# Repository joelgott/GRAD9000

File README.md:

# Description

This project is strongly inspired by the HAL9000 robot from Stanley Kubrick's 2001 Space Odyssey. I used an ESP32 based board for the main logic and an audio module so that it looks like it's talking. Most of the mechanical parts are recicled or 3D printed.
This repository contains all the contents for making and programming the robot.

## Hardware

This robot uses a [seed studio XIAO ESP32-c3 development board](https://wiki.seeedstudio.com/XIAO_ESP32C3_Getting_Started/) with a [DFPlayer audio module](https://www.dfrobot.com/product-1121.html). 
In the PCB folder there is a custom designed PCB that contains both boards, recieves a 5V input and has, a servo controller connector, an i2c bus output, a rgb led pinout and a speaker output. There is also a socket for an adxl345 accelerometer and other audio output that can go to an amplifier.

## Software

In the Circuitpython folder there is the code that runs on the robot. There are two files, the one called eyetest lets me play with the rgb led to try animations and such. The other one called grad9000 contains the logic for controlling the audio module, reading the json file and switching the green led while maintaining the red one permanently on so that it looks like it's talking. 

## Extras

I also made a python script that lets you generate a json file that contains the information of the audio files. This json file can then be uploaded to the robot so it knows the duration of each audio file and how many are in each folder.

## Contributing

Pull requests are welcome. For major changes, please open an issue first
to discuss what you would like to change.

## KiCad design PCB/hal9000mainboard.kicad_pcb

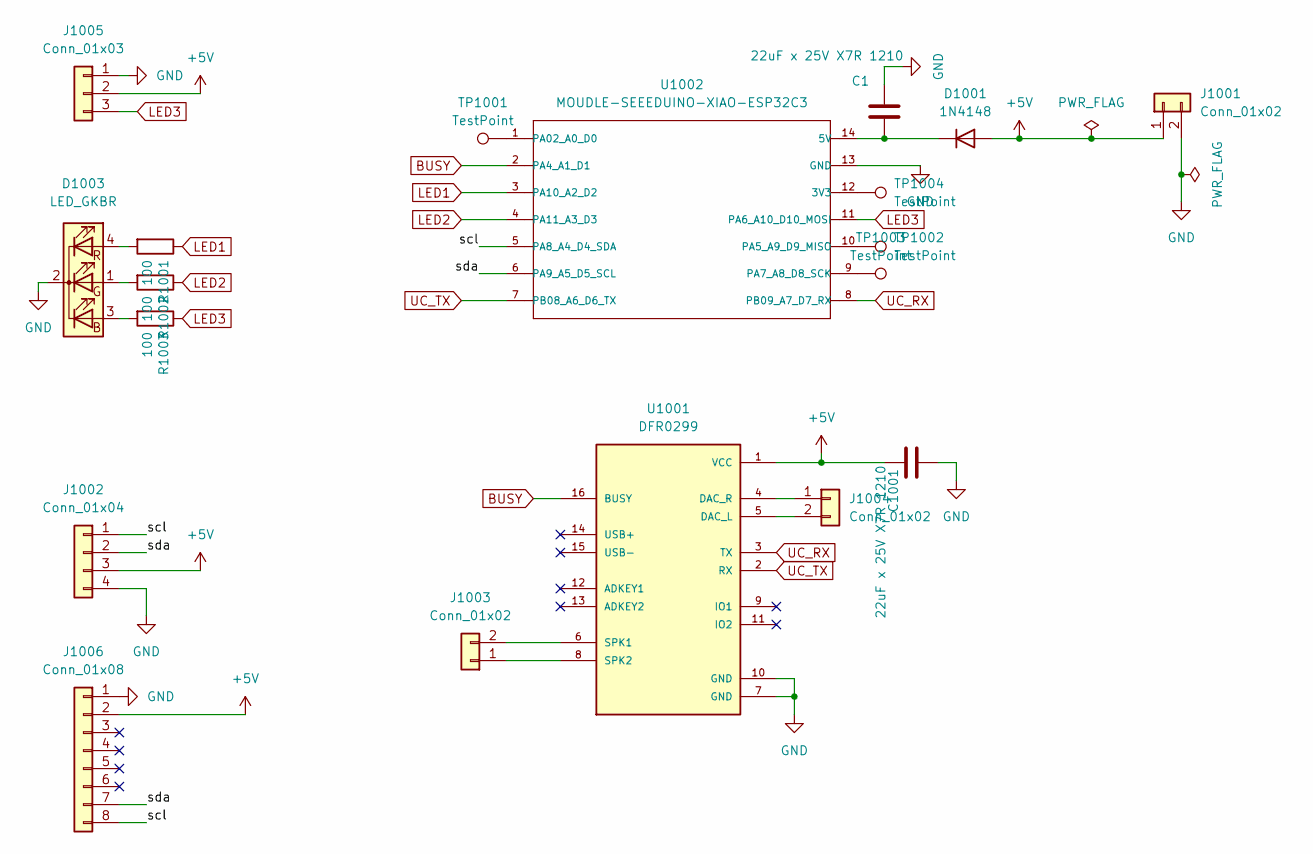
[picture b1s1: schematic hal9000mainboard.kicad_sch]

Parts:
C1, C1001: 22uF x 25V X7R 1210; C_Rect_L4.0mm_W2.5mm_P2.50mm; Digikey Code 1276-3392-1-ND
D1001: 1N4148; D_DO-35_SOD27_P7.62mm_Horizontal
D1003: LED_GKBR; LED_D5.0mm-4_RGB_Wide_Pins
J1001: Conn_01x02; PhoenixContact_MCV_1,5_2-G-3.81_1x02_P3.81mm_Vertical
J1002: Conn_01x04; PinHeader_1x04_P2.54mm_Vertical
J1003, J1004: Conn_01x02; TerminalBlock_bornier-2_P5.08mm
J1005: Conn_01x03; PinHeader_1x03_P2.54mm_Vertical
J1006: Conn_01x08; PinHeader_1x08_P2.54mm_Vertical
R1001, R1002, R1003: 100; R_0603_1608Metric; Digikey Code 2019-RK73H1JRTTD2200FCT-ND
TP1001, TP1002, TP1003, TP1004: TestPoint; TestPoint_Pad_3.0x3.0mm
U1001: DFR0299; MODULE_DFR0299
U1002: MOUDLE-SEEEDUINO-XIAO-ESP32C3; XIAO-Generic-Hybrid-14P-2.54-21X17.8MM

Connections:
+5V: C1001.1, D1001.2 (A), J1001.1, J1002.3, J1005.2, J1006.2, U1001.1 (VCC)
/scl: J1002.1, J1006.8, U1002.5 (PA8_A4_D4_SDA)
/sda: J1002.2, J1006.7, U1002.6 (PA9_A5_D5_SCL)
BUSY: U1001.16 (BUSY), U1002.2 (PA4_A1_D1)
GND: C1.2, C1001.2, D1003.2 (K), J1001.2, J1002.4, J1005.1, J1006.1, U1001.7 (GND), U1001.10 (GND), U1002.13 (GND)
LED1: R1001.1, U1002.3 (PA10_A2_D2)
LED2: R1002.1, U1002.4 (PA11_A3_D3)
LED3: J1005.3, R1003.1, U1002.11 (PA6_A10_D10_MOSI)
unnamed: C1.1, D1001.1 (K), U1002.14 (5V)
unnamed: D1003.3 (BA), R1003.2
unnamed: D1003.1 (GA), R1002.2
unnamed: D1003.4 (RA), R1001.2
unnamed: J1003.1, U1001.8 (SPK2)
unnamed: J1003.2, U1001.6 (SPK1)
unnamed: J1004.1, U1001.4 (DAC_R)
unnamed: J1004.2, U1001.5 (DAC_L)
unnamed: TP1004.1, U1002.12 (3V3)
unnamed: TP1001.1, U1002.1 (PA02_A0_D0)
unnamed: TP1002.1, U1002.10 (PA5_A9_D9_MISO)
unnamed: TP1003.1, U1002.9 (PA7_A8_D8_SCK)
UC_RX: U1001.3 (TX), U1002.8 (PB09_A7_D7_RX)
UC_TX: U1001.2 (RX), U1002.7 (PB08_A6_D6_TX)

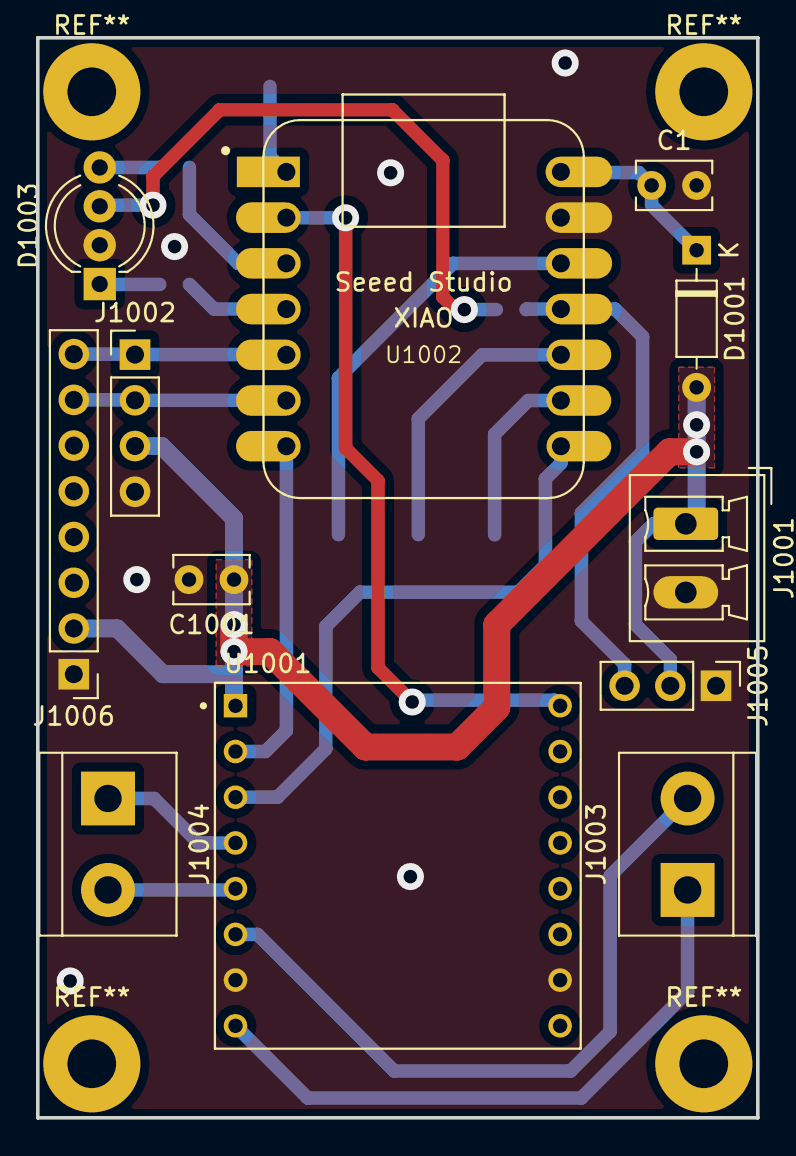
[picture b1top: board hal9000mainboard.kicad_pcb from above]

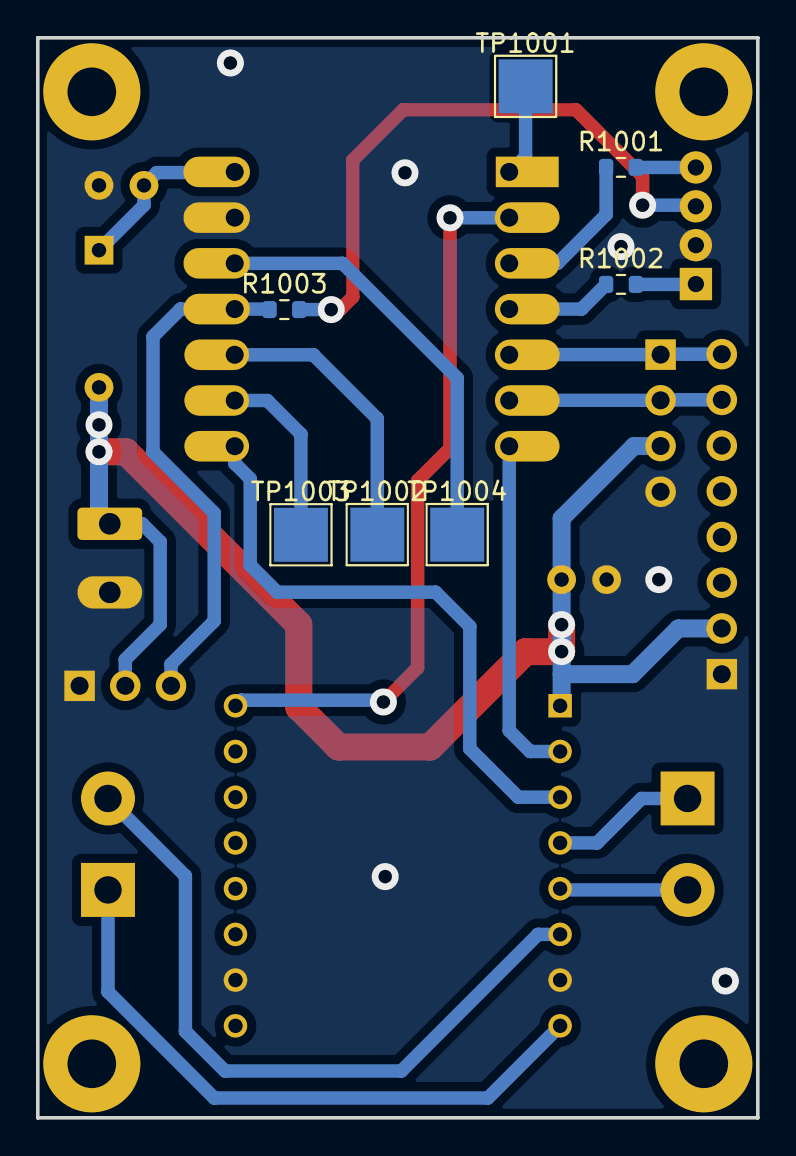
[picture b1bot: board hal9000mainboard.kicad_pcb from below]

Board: 2 copper layers, 40.0 x 60.0 mm, 19 parts (7 on the bottom side), 22 nets.

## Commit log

2024-11-16 adxl345 fix, renaming, and song playing
